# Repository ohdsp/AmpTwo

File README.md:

# [Open Hardware DSP Platform](http://www.ohdsp.org)
## AmpTwo
### Revision 1.0

---
# README
### Disclaimer
Copyright Paul Janicki 2017

Licensed under the TAPR Open Hardware License (www.tapr.org/OHL)

This documentation is distributed WITHOUT ANY EXPRESS OR IMPLIED WARRANTY, INCLUDING OF MERCHANTABILITY, SATISFACTORY QUALITY AND FITNESS FOR A PARTICULAR PURPOSE.

### What is this repository?

**Quick summary**

This is Open Hardware DSP Platform AmpTwo Module. 

This is a dual independant stereo headphone amplifier with analogue volume control. All 4 channels are fed from different DAC outputs from the ADAU1966 DAC module.

This repository contains the KiCad design files, manufacturing Gerber/drill files, PDF/drawing files, and relevant documenation for this board.

### What is the project folder structure?
Most folder names are self explanatory. Starting from the top level: \
*AmpTwo*
+ *Bill of Materials*  - This contains the bill of materials in CVS, LibreOffice Calc and XML formats
+ *Drawings*  - This contains PDF and SVG outputs of schematic and PCB files
+ *Gerbers* - This contains the PCB Gerbers and drill drawings for manufacture, there is also a zip file ready to send to most manufacturers
+ *KiCad* - This contains the original KiCad schematic and PCB design files
+ *Pick-Place and Stencil* - This contains the pick and place file for automated placement of PCB components and the pasate/stencil layer to make a solder paste stencil 

### How do I get set up?

**Summary of set up**

1. Set your self up a directory on a local disk, something simple will make life easier (eg C:\Electronics on Windows as used here), but anywhere will do just fine.
2. Download the Kicad-Libs from [https://github.com/ohdsp/KiCad-Libs](https://github.com/ohdsp/KiCad-Libs) and place in C:\Electronics\Kicad-Libs (or your chosen folder) 
3. Create a OHDSP subdirectory in C:\Electronics (so C:\Electronics\OHDSP)
3. Download this project to C:\Electronics\OHDSP\AmpTwo
4. Fire up Kicad
5. Open the main project file C:\Electronics\OHDSP\AmpTwo\KiCad\AmpTwo.pro
6. (Optional) Setup Pcbnew component library as below.
7. Do as you wish with the project, just keep it under TAPR Open Hardware License

Make sure your git setup doesn't exclude files used in the project (like .LIB files) or things may go wrong down the line.

**KiCad Library Configuration**

Note that you need to setup a Pcbnew library, but the eeschema libraries should work without any changes if you followed the instructions above.

To setup Pcbnew libraries:

In Pcbnew go to Preferences -> Footprint Libraries Manager. Under Global Libraries tab in the top list check if there is a nickname "MyKiCadLibs-Footprints" (usually at the end of the list). If there is but it points to the wrong place then change the Library Path to point to MyKiCadLibs-Footprints (eg C:\Electronics\KiCad-Libs\MyKiCadLibs-Footprints.pretty) folder for your setup. If this is missing you can use "Append with Wizard", choose "Files on my computer", click next, browse to library location (eg C:\Electronics\KiCad-Libs\MyKiCadLibs-Footprints.pretty) and select the folder MyKiCadLibs-Footprints.pretty, click next, check the Status column states OK and the Format is KiCad (if not re-download the library) and click next, then select "To global library configuration..." and click Finish.

To setup eeschema component libraries:
Either from KiCad project window go to Tools -> Run Library Editor OR under eeschema, go to Tools -> Library Editor. Then Preferences -> Component Libraries.

The top section "Component Library Files" should ideally contain only two libraries, the "power" library that ships with KiCad and "MyKiCadLibs-Lib" available from above. To setup MyKiCadLibs-Lib as a relative path under the "User defined search path" click add. Browse to the location of KiCad-Libs you download above (eg C:\Electronics\KiCad-Libs) and click "Select Folder". Say yes to add a relative path. Under component library files click add, browse to the KiCad-libs again (eg C:\Electronics\KiCad-Libs), select file "MyKiCadLibs-Lib.lib" and click open. MyKiCadLibs-lib should appear in the component library list with no path as it will be using the user defined search path set in the box below.

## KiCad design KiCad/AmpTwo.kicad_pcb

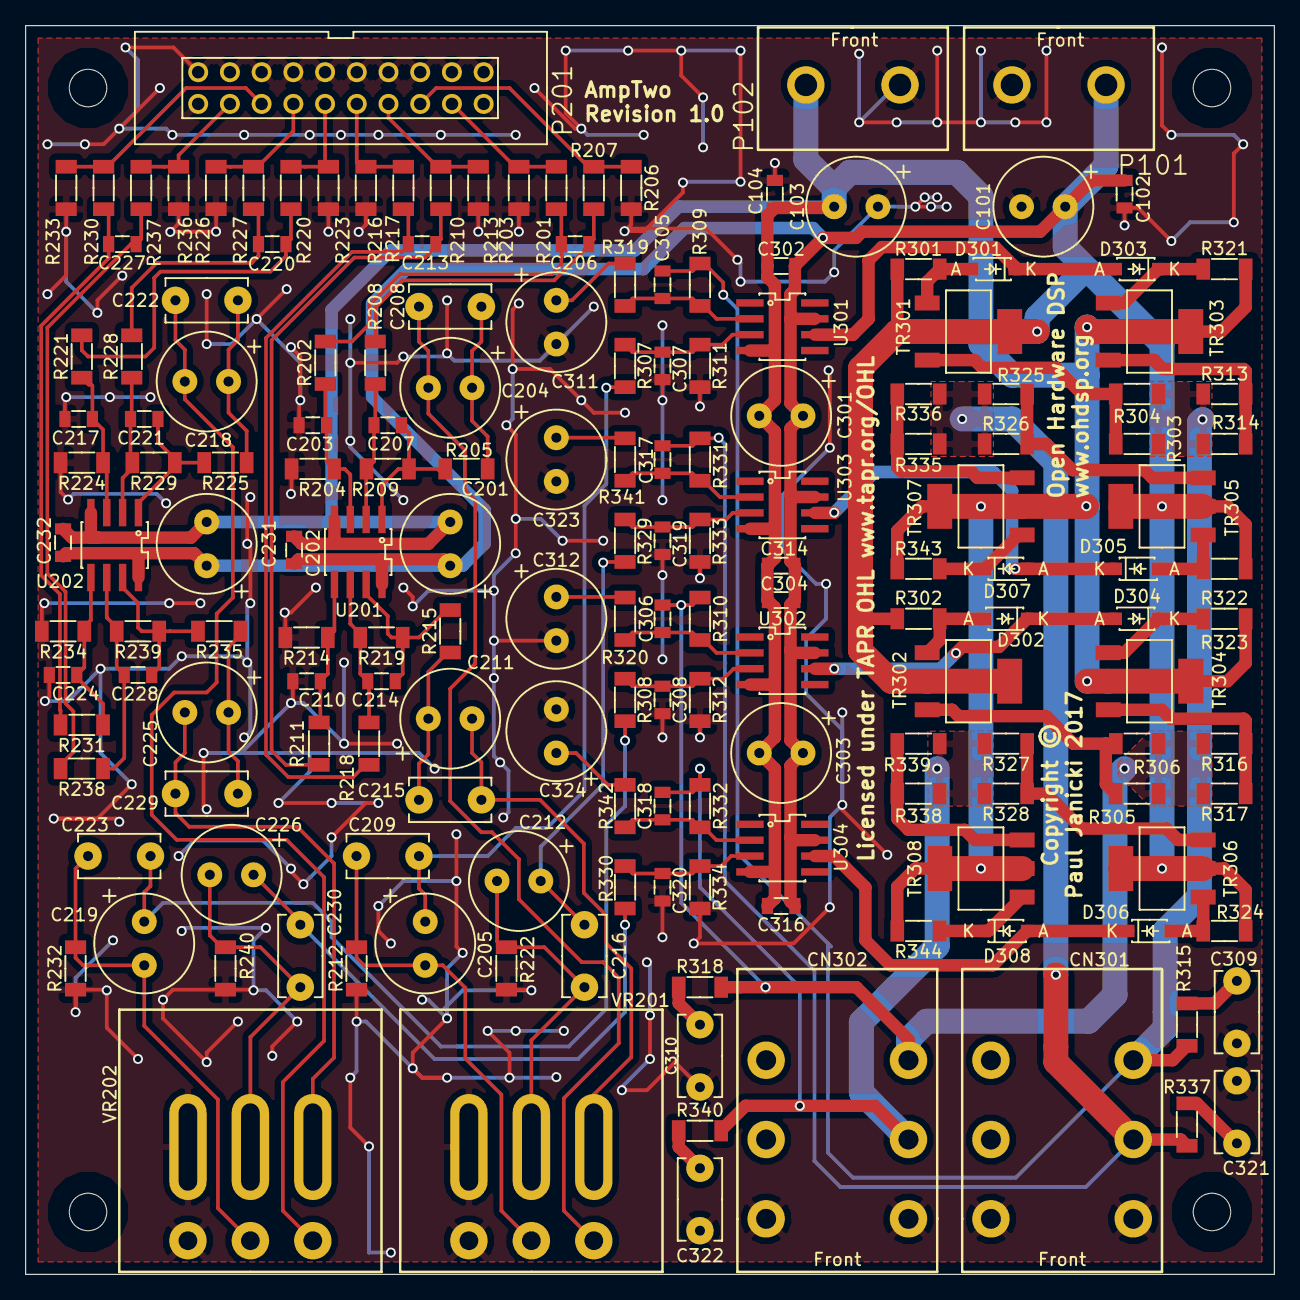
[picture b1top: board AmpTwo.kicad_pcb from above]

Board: 2 copper layers, 100.0 x 100.0 mm, 175 parts (0 on the bottom side), 87 nets.

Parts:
C101, C103, C201, C231, C301, C303, C311, C312, C323, C324: 220u; CAP-TH-D8mmP3.5mm
C102, C104, C202, C232, C302, C304, C314, C316: 100n; SMD-0805
C203, C206, C207, C210, C213, C214, C217, C220, C221, C224, C227, C228: 1n; SMD-0805
C204, C205, C211, C212, C218, C219, C225, C226: 100u; CAP-TH-D8mmP3.5mm
C208, C209, C215, C216, C222, C223, C229, C230, C309, C310, C321, C322: 100n; CAP_TH_5mm_W3.5mm
C305, C306, C307, C308, C317, C318, C319, C320: 220p; SMD-0805
CN301, CN302: CONN_6.35mm_SW_FCR11155_ACJS-MHDR; CON-6.35mm-ACJS-MHDR-FCR11155
D301, D302, D303, D304, D305, D306, D307, D308: 1N4148W; DIODE-SOD-123
MNT101, MNT102, MNT103, MNT104: MNT_HOLE; MNT_HOLE_3mm
P101, P102: CONN_2x1; CONN-SCREW-2WAY-7.5mm-7.62mm
P201: CONN_02X10; CONN_DIL_2X10_BOX_1MM
R201, R205, R207, R210, R215, R217, R220, R225, R227, R230, R235, R237: 100; SMD-1206
R202, R208, R211, R218, R221, R228, R231, R238: 1k3; SMD-1206
R203, R206, R213, R216, R223, R226, R233, R236: 100k; SMD-1206
R204, R209, R214, R219, R224, R229, R234, R239: 1k5; SMD-1206
R212, R222, R232, R240: 22k; SMD-1206
R301, R302, R321, R322, R323, R324, R343, R344: 4k7; SMD-1206
R303, R304, R305, R306, R313, R314, R315, R316, R317, R318, R325, R326, R327, R328, R335, R336, R337, R338, R339, R340: 10; SMD-1206
R307, R308, R309, R310, R311, R312, R319, R320, R329, R330, R331, R332, R333, R334, R341, R342: 10k; SMD-1206
TR301, TR302, TR305, TR306: BCP56−16; IC-SOT-223
TR303, TR304, TR307, TR308: BCP53−16; IC-SOT-223
U201, U202: TLE2082; IC_SOIC_8
U301, U302, U303, U304: TLE2081; IC_SOIC_8
VR201, VR202: 100k; POT_DUAL_16mm_17mm_20mm

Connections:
+9VA: C101.1, C102.2, C201.1, C202.2, C231.1, C232.2, C301.1, C302.2, C303.1, C304.2, C314.2, C316.2, P101.1, R301.1, R302.1, R323.1, R324.1, TR301.2, TR302.2, TR305.2, TR306.2, U201.8, U202.8, U301.7, U302.7, U303.7, U304.7
-9VA: C103.2, C104.1, C201.2, C202.1, C231.2, C232.1, C301.2, C302.1, C303.2, C304.1, C314.1, C316.1, P102.2, R321.2, R322.2, R343.2, R344.2, TR303.2, TR304.2, TR307.2, TR308.2, U201.4, U202.4, U301.4, U302.4, U303.4, U304.4
/DiscreteHeadAmp/IN_1: C205.1, C209.1, R307.2
/DiscreteHeadAmp/IN_2: C212.1, C216.1, R329.2
/DiscreteHeadAmp/IN_3: C219.1, C223.1, R308.2
/DiscreteHeadAmp/IN_4: C226.1, C230.1, R330.2
GNDD: C101.2, C102.1, C103.1, C104.2, C203.2, C210.2, C217.2, C224.2, C307.2, C308.2, C309.1, C310.1, C311.2, C312.2, C319.2, C320.2, C321.1, C322.1, C323.2, C324.2, CN301.1, CN301.4, CN302.1, CN302.4, P101.2, P102.1, P201.1, P201.2, P201.3, P201.5, P201.7, P201.9, P201.11, P201.13, P201.15, P201.17, P201.19, P201.20, R203.2, R204.2, R206.2, R212.1, R213.2, R214.2, R216.2, R222.1, R223.2, R224.2, R226.2, R232.1, R233.2, R234.2, R236.2, R240.1, R311.2, R312.2, R333.2, R334.2, VR201.1, VR201.4, VR202.1, VR202.4
unnamed: C203.1, R202.1, R204.1, U201.3
unnamed: C204.1, C208.2, R205.1
unnamed: C204.2, C208.1, VR201.3
unnamed: C205.2, C209.2, R212.2, VR201.2
unnamed: C206.1, R201.1, R202.2
unnamed: C206.2, R207.1, R208.2
unnamed: C207.1, R205.2, R209.1, U201.1
unnamed: C207.2, R208.1, R209.2, U201.2
unnamed: C210.1, R211.1, R214.1, U201.5
unnamed: C211.1, C215.2, R215.1
unnamed: C211.2, C215.1, VR201.6
unnamed: C212.2, C216.2, R222.2, VR201.5
unnamed: C213.1, R210.1, R211.2
unnamed: C213.2, R217.1, R218.2
unnamed: C214.1, R215.2, R219.1, U201.7
unnamed: C214.2, R218.1, R219.2, U201.6
unnamed: C217.1, R221.1, R224.1, U202.3
unnamed: C218.1, C222.2, R225.1
unnamed: C218.2, C222.1, VR202.3
unnamed: C219.2, C223.2, R232.2, VR202.2
unnamed: C220.1, R220.1, R221.2
unnamed: C220.2, R227.1, R228.2
unnamed: C221.1, R225.2, R229.1, U202.1
unnamed: C221.2, R228.1, R229.2, U202.2
unnamed: C224.1, R231.1, R234.1, U202.5
unnamed: C225.1, C229.2, R235.1
unnamed: C225.2, C229.1, VR202.6
unnamed: C226.2, C230.2, R240.2, VR202.5
unnamed: C227.1, R230.1, R231.2
unnamed: C227.2, R237.1, R238.2
unnamed: C228.1, R235.2, R239.1, U202.7
unnamed: C228.2, R238.1, R239.2, U202.6
unnamed: C305.1, R309.2, R319.1, U301.2
unnamed: C305.2, CN301.6, R303.2, R304.2, R309.1, R313.2, R314.2, R315.2
unnamed: C306.1, R310.2, R320.1, U302.2
unnamed: C306.2, CN302.6, R305.2, R306.2, R310.1, R316.2, R317.2, R318.2
unnamed: C307.1, R307.1, R311.1, U301.3
unnamed: C308.1, R308.1, R312.1, U302.3
unnamed: C309.2, R315.1
unnamed: C310.2, R318.1
unnamed: C311.1, R319.2
unnamed: C312.1, R320.2
unnamed: C317.1, R331.2, R341.1, U303.2
unnamed: C317.2, CN301.5, R325.2, R326.2, R331.1, R335.2, R336.2, R337.2
unnamed: C318.1, R332.2, R342.1, U304.2
unnamed: C318.2, CN302.5, R327.2, R328.2, R332.1, R338.2, R339.2, R340.2
unnamed: C319.1, R329.1, R333.1, U303.3
unnamed: C320.1, R330.1, R334.1, U304.3
unnamed: C321.2, R337.1
unnamed: C322.2, R340.1
unnamed: C323.1, R341.2
unnamed: C324.1, R342.2
unnamed: D301.1, R301.2, TR301.1
unnamed: D301.2, D303.1, U301.6
unnamed: D302.1, R302.2, TR302.1
unnamed: D302.2, D304.1, U302.6
unnamed: D303.2, R321.1, TR303.1
unnamed: D304.2, R322.1, TR304.1
unnamed: D305.1, R323.2, TR305.1
unnamed: D305.2, D307.1, U303.6
unnamed: D306.1, R324.2, TR306.1
unnamed: D306.2, D308.1, U304.6
unnamed: D307.2, R343.1, TR307.1
unnamed: D308.2, R344.1, TR308.1
unnamed: P201.4, R201.2, R203.1
unnamed: P201.6, R206.1, R207.2
unnamed: P201.8, R210.2, R213.1
unnamed: P201.10, R216.1, R217.2
unnamed: P201.12, R220.2, R223.1
unnamed: P201.14, R226.1, R227.2
unnamed: P201.16, R230.2, R233.1
unnamed: P201.18, R236.1, R237.2
unnamed: R303.1, R304.1, TR301.3
unnamed: R305.1, R306.1, TR302.3
unnamed: R313.1, R314.1, TR303.3
unnamed: R316.1, R317.1, TR304.3
unnamed: R325.1, R326.1, TR305.3
unnamed: R327.1, R328.1, TR306.3
unnamed: R335.1, R336.1, TR307.3
unnamed: R338.1, R339.1, TR308.3

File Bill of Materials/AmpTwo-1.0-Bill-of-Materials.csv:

Reference; Quantity; Footprint; Value; Description; Voltage; Type; Tolerance; Size; Power; 
C101 C103 C201 C231 C301 C303 ;6;CAP-TH-D8mmP3.5mm;220u;'Aluminium electrolytic capacitor;'35V;';';'Pitch 3.5mm, Diameter 8mm;';
C102 C104 C202 C232 C302 C304 C314 C316 ;8;SMD-0805;100n;'Ceramic capacitor;'50V;'X7R;'10%;'0805;';
C204 C205 C211 C212 C218 C219 C225 C226 ;8;CAP-TH-D8mmP3.5mm;100u;'High quality capacitor, eg Panasonic FC;'35V;';';'Pitch 3.5mm, Diameter 8mm;';
C203 C206 C207 C210 C213 C214 C217 C220 C221 C224 C227 C228 ;12;SMD-0805;1n;'Ceramic capacitor;'50V;'C0G;'5%;'0805;';
C208 C209 C215 C216 C222 C223 C229 C230 C309 C310 C321 C322 ;12;CAP_TH_5mm_W3.5mm;100n;'Polyester film capacitor;'63V;'MKT;'5%;'5mm;';
C305 C306 C307 C308 C317 C318 C319 C320 ;8;SMD-0805;220p;'Ceramic capacitor;'50V;'C0G;'5%;'0805;';
C311 C312 C323 C324 ;4;CAP-TH-D8mmP3.5mm;220u;'High quality capacitor, eg Panasonic FC;'35V;';';'Pitch 3.5mm, Diameter 8mm;';
CN301 CN302 ;2;CON-6.35mm-ACJS-MHDR-FCR11155;CONN_6.35mm_SW_FCR11155_ACJS-MHDR;'6.35mm PCB Mount Jack - Examples Cliff FCR11155 or AMPHENOL ACJS-MHDR;';';';';';
D301 D302 D303 D304 D305 D306 D307 D308 ;8;DIODE-SOD-123;1N4148W;'Any 1N4148 SOD-123 Diode;';';';';';
P101 P102 ;2;CONN-SCREW-2WAY-7.5mm-7.62mm;CONN_2x1;'7.5mm or 7.62mm pitch 2 way screw terminal;';';';';';
P201 ;1;CONN_DIL_2X10_BOX_1MM;CONN_02X10;'2x10 2.54mm pitch box header;';';';';';
R202 R208 R211 R218 R221 R228 R231 R238 ;8;SMD-1206;1k3;'MELF0204 or 1206;';';'1%;'1206;'250mW;
R204 R209 R214 R219 R224 R229 R234 R239 ;8;SMD-1206;1k5;'MELF0204 or 1206;';';'1%;'1206;'250mW;
R212 R222 R232 R240 ;4;SMD-1206;22k;'MELF0204 or 1206;';';'1%;'1206;'250mW;
R203 R206 R213 R216 R223 R226 R233 R236 ;8;SMD-1206;100k;'MELF0204 or 1206;';';'1%;'1206;'250mW;
R201 R205 R207 R210 R215 R217 R220 R225 R227 R230 R235 R237 ;12;SMD-1206;100;'MELF0204 or 1206;';';'1%;'1206;'250mW;
R301 R302 R321 R322 R323 R324 R343 R344 ;8;SMD-1206;4k7;'MELF0204 or 1206;';';'1%;'1206;'250mW;
R303 R304 R305 R306 R313 R314 R315 R316 R317 R318 R325 R326 R327 R328 R335 R336 R337 R338 R339 R340 ;20;SMD-1206;10;'MELF0204 or 1206;';';'1%;'1206;'250mW;
R307 R308 R309 R310 R311 R312 R319 R320 R329 R330 R331 R332 R333 R334 R341 R342 ;16;SMD-1206;10k;'MELF0204 or 1206;';';'1%;'1206;'250mW;
TR301 TR302 TR305 TR306 ;4;IC-SOT-223;BCP56-16;'NPN Transistor;'80V;'1A;;;'1.5W;
TR303 TR304 TR307 TR308 ;4;IC-SOT-223;BCP53-16;'PNP Transistor;'80V;'1A;;;'1.5W;
U201 U202 ;2;IC_SOIC_8;TLE2082;Any high quality dual op-amp;'36V;;;;;
U301 U302 U303 U304 ;4;IC_SOIC_8;TLE2081;Any high quality single op-amp;'36V;;;;;
VR201 VR202 ;2;POT_DUAL_16mm_17mm_20mm;100k;'Any 16mm, 17mm or 20mm linear dual gang potentiometer;';';20%;';';

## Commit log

2017-03-24 Release 1.0
    Release 1.0

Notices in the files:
KiCad/AmpTwo.kicad_pcb:
Copyright ©
Licensed under TAPR OHL www.tapr.org/OHL
